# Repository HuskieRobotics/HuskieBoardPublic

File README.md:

# The Huskie Board
## Overview
The Huskie Board, designed by Team 3061, is an FRC qualified expansion board for the
NI roboRIO robotics controller. In addition to breaking out all available signals on the
MXP expansion port, this board uses a Parallax Propeller chip (8 symmetrical logical
cores with shared memory and peripheral access) to enable tasks such as advanced
data logging, on-field driver control and status, and NeoPixel control. Additional GPIO
and analog inputs are added with open source code to allow further customization.

## Firmware
The Huskie Board's firmware is stored on a 32 KB Flash chip. It can be upgraded over USB, and teams are welcome to load their own firmware. All Huskie Board firmware is stored in the `propeller firmware/` directory.

## roboRIO software
The LabView firmware is available in the `LabView/LabVIEW API/` directory. This includes examples in the `Examples/` folder, and the API source code in the `Huskie Board/` folder. See `install.txt` for more information.

Currently, the roboRIO API is only available for labview, though we hope to port it for C++ and Java soon.

## Hardware
The Huskie Board was designed in Eagle CAD, and sources are available in `Eagle CAD/projects/HuskieBoard/`.

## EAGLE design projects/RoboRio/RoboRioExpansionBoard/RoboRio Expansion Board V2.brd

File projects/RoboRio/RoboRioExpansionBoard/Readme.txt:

Fab Drawing                    | Fab.pdf
Assy Drawing                   | Assy.pdf
Fab Array Drawing, no holes    | Fab_1x3A.pdf
Fab Array Drawing, with holes  | Fab_1x3B.pdf

Top Copper                     | RoboRIO Expansion Board V2.GTL
Bottom Copper                  | RoboRIO Expansion Board V2.GBL
Top Silkscreen                 | RoboRIO Expansion Board V2.GTO
Top Paste                      | RoboRIO Expansion Board V2.GTP
Top Soldermask                 | RoboRIO Expansion Board V2.GTS
Bottom Soldermask              | RoboRIO Expansion Board V2.GBS
Drill File                     | RoboRIO Expansion Board V2.TXT
Mill Layer                     | RoboRIO Expansion Board V2.GML

centroid file                  | RoboRIO Expansion Board V2_centroid.csv

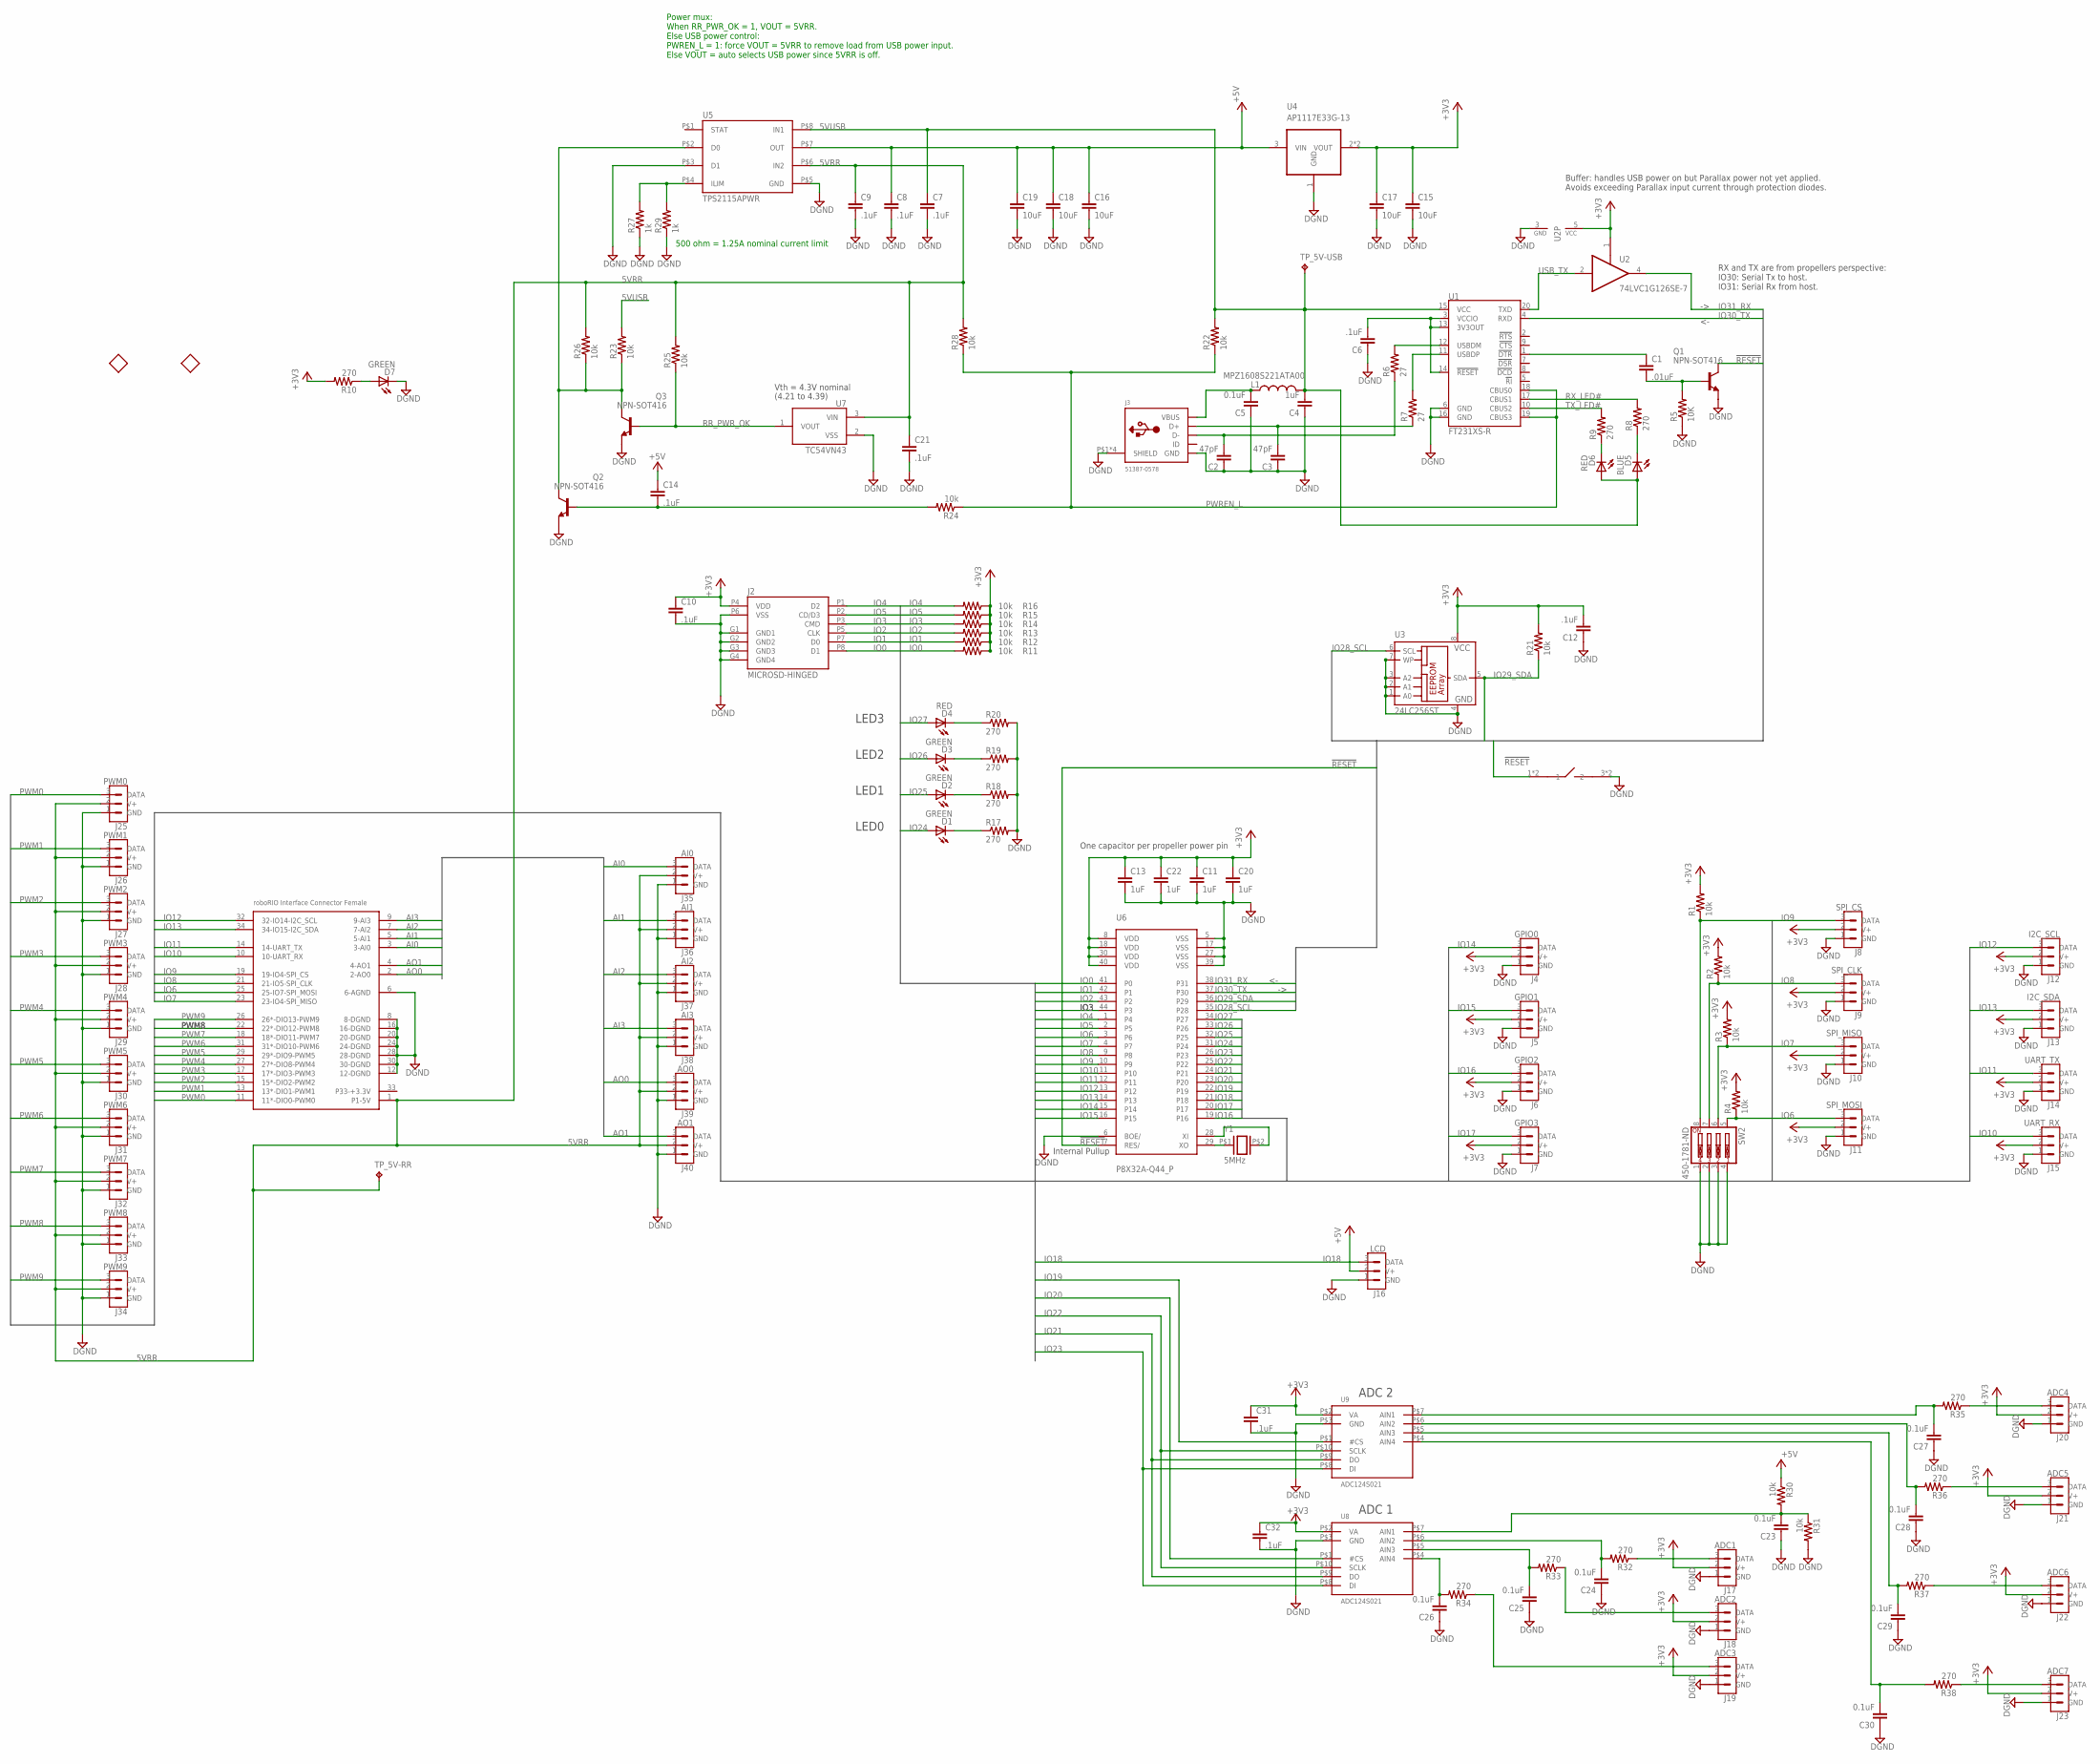
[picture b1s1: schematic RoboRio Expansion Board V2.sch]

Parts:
C1: .01uF; C0603K
C2, C3: 47pF; C0603K
C4, C11, C13, C20, C22: 1uF; C0603K
C5, C23, C24, C25, C26, C27, C28, C29, C30: 0.1uF; C0603K
C6, C7, C8, C9, C10, C12, C14, C21, C31, C32: .1uF; C0603K
C15, C16, C17, C18, C19: 10uF; C0805K
D1, D2, D3, D7: GREEN; CHIPLED_0603
D4, D6: RED; CHIPLED_0603
D5: BLUE; CHIPLED_0603
J1: RRINTERFACE-FEMALE; RRINT-FEMALE
J2: MICROSD-HINGED; MICRO_SD_HINGED_TYPE
J3: 51387-0578; USB-MINIB-0513870578
J4: GPIO0; 3PINPACKAGE
J5: GPIO1; 3PINPACKAGE
J6: GPIO2; 3PINPACKAGE
J7: GPIO3; 3PINPACKAGE
J8: SPI_CS; 3PINPACKAGE
J9: SPI_CLK; 3PINPACKAGE
J10: SPI_MISO; 3PINPACKAGE
J11: SPI_MOSI; 3PINPACKAGE
J12: I2C_SCL; 3PINPACKAGE
J13: I2C_SDA; 3PINPACKAGE
J14: UART_TX; 3PINPACKAGE
J15: UART_RX; 3PINPACKAGE
J16: LCD; 3PINPACKAGE
J17: ADC1; 3PINPACKAGE
J18: ADC2; 3PINPACKAGE
J19: ADC3; 3PINPACKAGE
J20: ADC4; 3PINPACKAGE
J21: ADC5; 3PINPACKAGE
J22: ADC6; 3PINPACKAGE
J23: ADC7; 3PINPACKAGE
J25: PWM0; 3PINPACKAGE
J26: PWM1; 3PINPACKAGE
J27: PWM2; 3PINPACKAGE
J28: PWM3; 3PINPACKAGE
J29: PWM4; 3PINPACKAGE
J30: PWM5; 3PINPACKAGE
J31: PWM6; 3PINPACKAGE
J32: PWM7; 3PINPACKAGE
J33: PWM8; 3PINPACKAGE
J34: PWM9; 3PINPACKAGE
J35: AI0; 3PINPACKAGE
J36: AI1; 3PINPACKAGE
J37: AI2; 3PINPACKAGE
J38: AI3; 3PINPACKAGE
J39: AO0; 3PINPACKAGE
J40: AO1; 3PINPACKAGE
L1: MPZ1608S221ATA00; 0603
Q1, Q2, Q3: NPN-SOT416; SC75_INFINEON
R1, R2, R3, R4, R11, R12, R13, R14, R15, R16, R21, R22, R23, R24, R25, R26, R28, R30, R31: 10k; R0603
R5: 10K; R0603
R6, R7: 27; R0603
R8, R9, R10, R17, R18, R19, R20, R32, R33, R34, R35, R36, R37, R38: 270; R0603
R27, R29: 1k; R0603
SW1: RESETBUTTON9001DEFAULT; RESETBUTTON9001
SW2: 450-1781-ND; EDG-04
TP_5V-RR, TP_5V-USB: TPPAD1-17; P1-17
U1: FT231XS-R; SSOP20_L
U2: 74LVC1G126SE-7; SC70-5
U3: 24LC256ST; TSSOP8
U4: AP1117E33G-13; SOT223; MPN AP1117E33G-13
U5: TPS2115APWR; TSSOP-8
U6: P8X32A-Q44_P; P8X32A-Q44
U7: TC54VN43; SOT23
U8, U9: ADC124S021; ADC124S021VSSOP
U$1, U$2: FIDUCIAL_DIAMOND; FIDUCIAL_40MIL_DIAMOND
Y1: 5MHz; HC\49US

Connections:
5VRR: C9.1, C21.1, J1.1 (P1-5V), J25.2 (V+), J26.2 (V+), J27.2 (V+), J28.2 (V+), J29.2 (V+), J30.2 (V+), J31.2 (V+), J32.2 (V+), J33.2 (V+), J34.2 (V+), J35.2 (V+), J36.2 (V+), J37.2 (V+), J38.2 (V+), J39.2 (V+), J40.2 (V+), R25.2, R26.2, R28.2, TP_5V-RR.TP, U5.P$6 (IN2), U7.3 (VIN)
5VUSB: C4.2, C7.1, D5.A, D6.A, L1.2, R22.2, R23.2, TP_5V-USB.TP, U1.15 (VCC), U5.P$8 (IN1)
!RESET: Q1.3 (C), SW1.1, SW1.2 (1), U6.7 (RES/)
+3V3: C10.1, C11.1, C12.2, C13.1, C15.1, C17.1, C20.1, C22.1, C31.1, C32.1, J2.P4 (VDD), J4.2 (V+), J5.2 (V+), J6.2 (V+), J7.2 (V+), J8.2 (V+), J9.2 (V+), J10.2 (V+), J11.2 (V+), J12.2 (V+), J13.2 (V+), J14.2 (V+), J15.2 (V+), J17.2 (V+), J18.2 (V+), J19.2 (V+), J20.2 (V+), J21.2 (V+), J22.2 (V+), J23.2 (V+), R1.2, R2.2, R3.2, R4.2, R10.2, R11.1, R12.1, R13.1, R14.1, R15.1, R16.1, R21.2, U2.1 (OE), U2.5 (VCC), U3.8 (VCC), U4.2 (VOUT), U4.4 (VOUT), U6.8 (VDD), U6.18 (VDD), U6.30 (VDD), U6.40 (VDD), U8.P$2 (VA), U9.P$2 (VA)
+5V: C8.1, C14.1, C16.1, C18.1, C19.1, J16.2 (V+), R30.1, U4.3 (VIN), U5.P$7 (OUT)
AI0: J1.3 (3-AI0), J35.3 (DATA)
AI1: J1.5 (5-AI1), J36.3 (DATA)
AI2: J1.7 (7-AI2), J37.3 (DATA)
AI3: J1.9 (9-AI3), J38.3 (DATA)
AO0: J1.2 (2-AO0), J39.3 (DATA)
AO1: J1.4 (4-AO1), J40.3 (DATA)
DGND: C2.1, C3.1, C4.1, C5.1, C6.1, C7.2, C8.2, C9.2, C10.2, C11.2, C12.1, C13.2, C15.2, C16.2, C17.2, C18.2, C19.2, C20.2, C21.2, C22.2, C23.1, C24.1, C25.1, C26.1, C27.1, C28.1, C29.1, C30.1, C31.2, C32.2, D7.C, J1.6 (6-AGND), J1.8 (8-DGND), J1.12 (12-DGND), J1.16 (16-DGND), J1.20 (20-DGND), J1.24 (24-DGND), J1.28 (28-DGND), J1.30 (30-DGND), J2.G1 (GND1), J2.G2 (GND2), J2.G3 (GND3), J2.G4 (GND4), J2.P6 (VSS), J3.GND, J3.P$1 (SHIELD), J3.P$2 (SHIELD), J3.P$3 (SHIELD), J3.P$4 (SHIELD), J4.1 (GND), J5.1 (GND), J6.1 (GND), J7.1 (GND), J8.1 (GND), J9.1 (GND), J10.1 (GND), J11.1 (GND), J12.1 (GND), J13.1 (GND), J14.1 (GND), J15.1 (GND), J16.1 (GND), J17.1 (GND), J18.1 (GND), J19.1 (GND), J20.1 (GND), J21.1 (GND), J22.1 (GND), J23.1 (GND), J25.1 (GND), J26.1 (GND), J27.1 (GND), J28.1 (GND), J29.1 (GND), J30.1 (GND), J31.1 (GND), J32.1 (GND), J33.1 (GND), J34.1 (GND), J35.1 (GND), J36.1 (GND), J37.1 (GND), J38.1 (GND), J39.1 (GND), J40.1 (GND), Q1.2 (E), Q2.2 (E), Q3.2 (E), R5.1, R17.2, R18.2, R19.2, R20.2, R27.1, R29.1, R31.2, SW1.3 (2), SW1.4 (2), SW2.1, SW2.2, SW2.3, SW2.4, U1.6 (GND), U1.16 (GND), U2.3 (GND), U3.1 (A0), U3.2 (A1), U3.3 (A2), U3.4 (GND), U3.7 (WP), U4.1 (GND), U5.P$3 (D1), U5.P$5 (GND), U6.5 (VSS), U6.6 (BOE/), U6.17 (VSS), U6.27 (VSS), U6.39 (VSS), U7.2 (VSS), U8.P$3 (GND), U9.P$3 (GND)
IO0: J2.P8 (D1), R11.2, U6.41 (P0)
IO1: J2.P7 (D0), R12.2, U6.42 (P1)
IO2: J2.P5 (CLK), R13.2, U6.43 (P2)
IO3: J2.P3 (CMD), R14.2, U6.44 (P3)
IO4: J2.P1 (D2), R16.2, U6.1 (P4)
IO5: J2.P2 (CD/D3), R15.2, U6.2 (P5)
IO6: J1.25 (25-IO7-SPI_MOSI), J11.3 (DATA), R4.1, SW2.5, U6.3 (P6)
IO7: J1.23 (23-IO4-SPI_MISO), J10.3 (DATA), R3.1, SW2.6, U6.4 (P7)
IO8: J1.21 (21-IO5-SPI_CLK), J9.3 (DATA), R2.1, SW2.7, U6.9 (P8)
IO9: J1.19 (19-IO4-SPI_CS), J8.3 (DATA), R1.1, SW2.8, U6.10 (P9)
IO10: J1.10 (10-UART_RX), J15.3 (DATA), U6.11 (P10)
IO11: J1.14 (14-UART_TX), J14.3 (DATA), U6.12 (P11)
IO12: J1.32 (32-IO14-I2C_SCL), J12.3 (DATA), U6.13 (P12)
IO13: J1.34 (34-IO15-I2C_SDA), J13.3 (DATA), U6.14 (P13)
IO14: J4.3 (DATA), U6.15 (P14)
IO15: J5.3 (DATA), U6.16 (P15)
IO16: J6.3 (DATA), U6.19 (P16)
IO17: J7.3 (DATA), U6.20 (P17)
IO18: J16.3 (DATA), U6.21 (P18)
IO19: U6.22 (P19), U9.P$1 (#CS)
IO20: U6.23 (P20), U8.P$1 (#CS)
IO21: U6.24 (P21), U8.P$9 (DO), U9.P$9 (DO)
IO22: U6.25 (P22), U8.P$10 (SCLK), U9.P$10 (SCLK)
IO23: U6.26 (P23), U8.P$8 (DI), U9.P$8 (DI)
IO24: D1.A, U6.31 (P24)
IO25: D2.A, U6.32 (P25)
IO26: D3.A, U6.33 (P26)
IO27: D4.A, U6.34 (P27)
IO28_SCL: U3.6 (SCL), U6.35 (P28)
IO29_SDA: R21.1, U3.5 (SDA), U6.36 (P29)
IO30_TX: U1.4 (RXD), U6.37 (P30)
IO31_RX: U2.4 (O), U6.38 (P31)
unnamed: C3.2, J3.D+, R7.1
unnamed: C2.2, J3.D-, R6.1
unnamed: C6.2, U1.3 (VCCIO), U1.13 (3V3OUT), U1.14 (!RESET)
unnamed: D7.A, R10.1
unnamed: C14.2, Q2.1 (B), R24.2
unnamed: J19.3 (DATA), R34.1
unnamed: J18.3 (DATA), R33.1
unnamed: C30.2, R38.2, U9.P$4 (AIN4)
unnamed: R27.2, R29.2, U5.P$4 (ILIM)
unnamed: D4.C, R20.1
unnamed: D1.C, R17.1
unnamed: D2.C, R18.1
unnamed: C26.2, R34.2, U8.P$4 (AIN4)
unnamed: C24.2, R32.2, U8.P$6 (AIN2)
unnamed: D3.C, R19.1
unnamed: D6.C, R9.1
unnamed: C1.1, U1.1 (!DTR)
unnamed: Q2.3 (C), Q3.3 (C), R23.1, R26.1, U5.P$2 (D0)
unnamed: C25.2, R33.2, U8.P$5 (AIN3)
unnamed: J17.3 (DATA), R32.1
unnamed: D5.C, R8.1
unnamed: R6.2, U1.12 (USBDM)
unnamed: C23.2, R30.2, R31.1, U8.P$7 (AIN1)
unnamed: C1.2, Q1.1 (B), R5.2
unnamed: R7.2, U1.11 (USBDP)
unnamed: C5.2, J3.VBUS, L1.1
unnamed: C29.2, R37.2, U9.P$5 (AIN3)
unnamed: U6.29 (XO), Y1.P$1 (1)
unnamed: J23.3 (DATA), R38.1
unnamed: J22.3 (DATA), R37.1
unnamed: U6.28 (XI), Y1.P$2 (2)
unnamed: C28.2, R36.2, U9.P$6 (AIN2)
unnamed: J21.3 (DATA), R36.1
unnamed: C27.2, R35.2, U9.P$7 (AIN1)
unnamed: J20.3 (DATA), R35.1
PWM0: J1.11 (11*-DIO0-PWM0), J25.3 (DATA)
PWM1: J1.13 (13*-DIO1-PWM1), J26.3 (DATA)
PWM2: J1.15 (15*-DIO2-PWM2), J27.3 (DATA)
PWM3: J1.17 (17*-DIO3-PWM3), J28.3 (DATA)
PWM4: J1.27 (27*-DIO8-PWM4), J29.3 (DATA)
PWM5: J1.29 (29*-DIO9-PWM5), J30.3 (DATA)
PWM6: J1.31 (31*-DIO10-PWM6), J31.3 (DATA)
PWM7: J1.18 (18*-DIO11-PWM7), J32.3 (DATA)
PWM8: J1.22 (22*-DIO12-PWM8), J33.3 (DATA)
PWM9: J1.26 (26*-DIO13-PWM9), J34.3 (DATA)
PWREN_L: R22.1, R24.1, R28.1, U1.18 (CBUS0), U1.19 (CBUS3)
RR_PWR_OK: Q3.1 (B), R25.1, U7.1 (VOUT)
RX_LED#: R8.2, U1.17 (CBUS1)
TX_LED#: R9.2, U1.10 (CBUS2)
USB_TX: U1.20 (TXD), U2.2 (I)

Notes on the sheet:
500 ohm = 1.25A nominal current limit
Power mux: When RR_PWR_OK = 1, VOUT = 5VRR. Else USB power control: PWREN_L = 1: force VOUT = 5VRR to remove load from USB power input. Else VOUT = auto selects USB power since 5VRR is off.
RX and TX are from propellers perspective: IO30: Serial Tx to host. IO31: Serial Rx from host.
Internal Pullup
Vth = 4.3V nominal
(4.21 to 4.39)
ADC 1
ADC 2
LED0
LED1
LED2
LED3
One capacitor per propeller power pin
Buffer: handles USB power on but Parallax power not yet applied. Avoids exceeding Parallax input current through protection diodes.

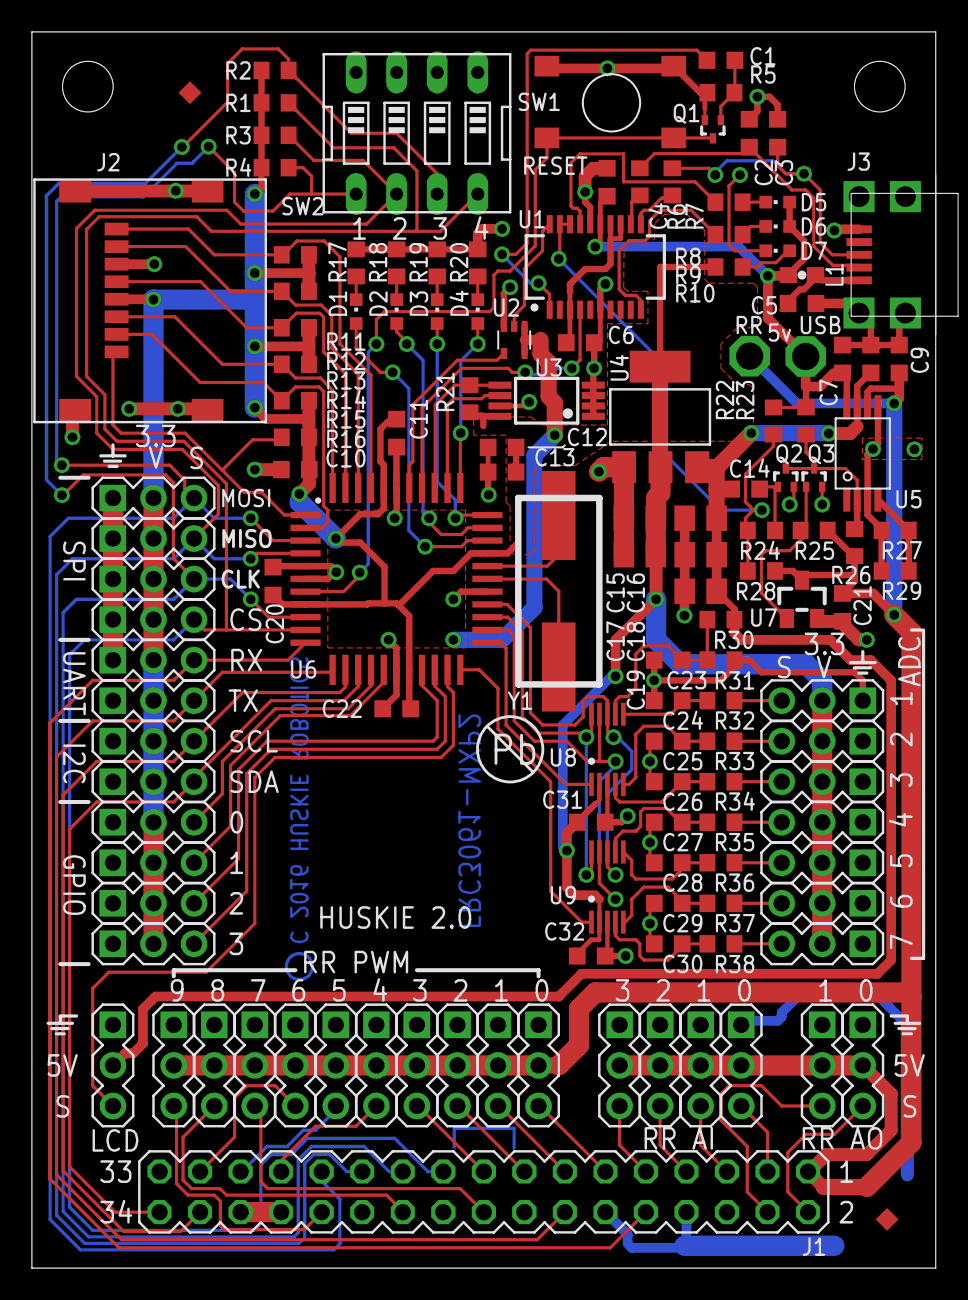
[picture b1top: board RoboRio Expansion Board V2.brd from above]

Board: 2 copper layers, 56.6 x 77.5 mm, 137 parts (0 on the bottom side), 94 nets.

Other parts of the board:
DRILEGEND: DRILEGEND

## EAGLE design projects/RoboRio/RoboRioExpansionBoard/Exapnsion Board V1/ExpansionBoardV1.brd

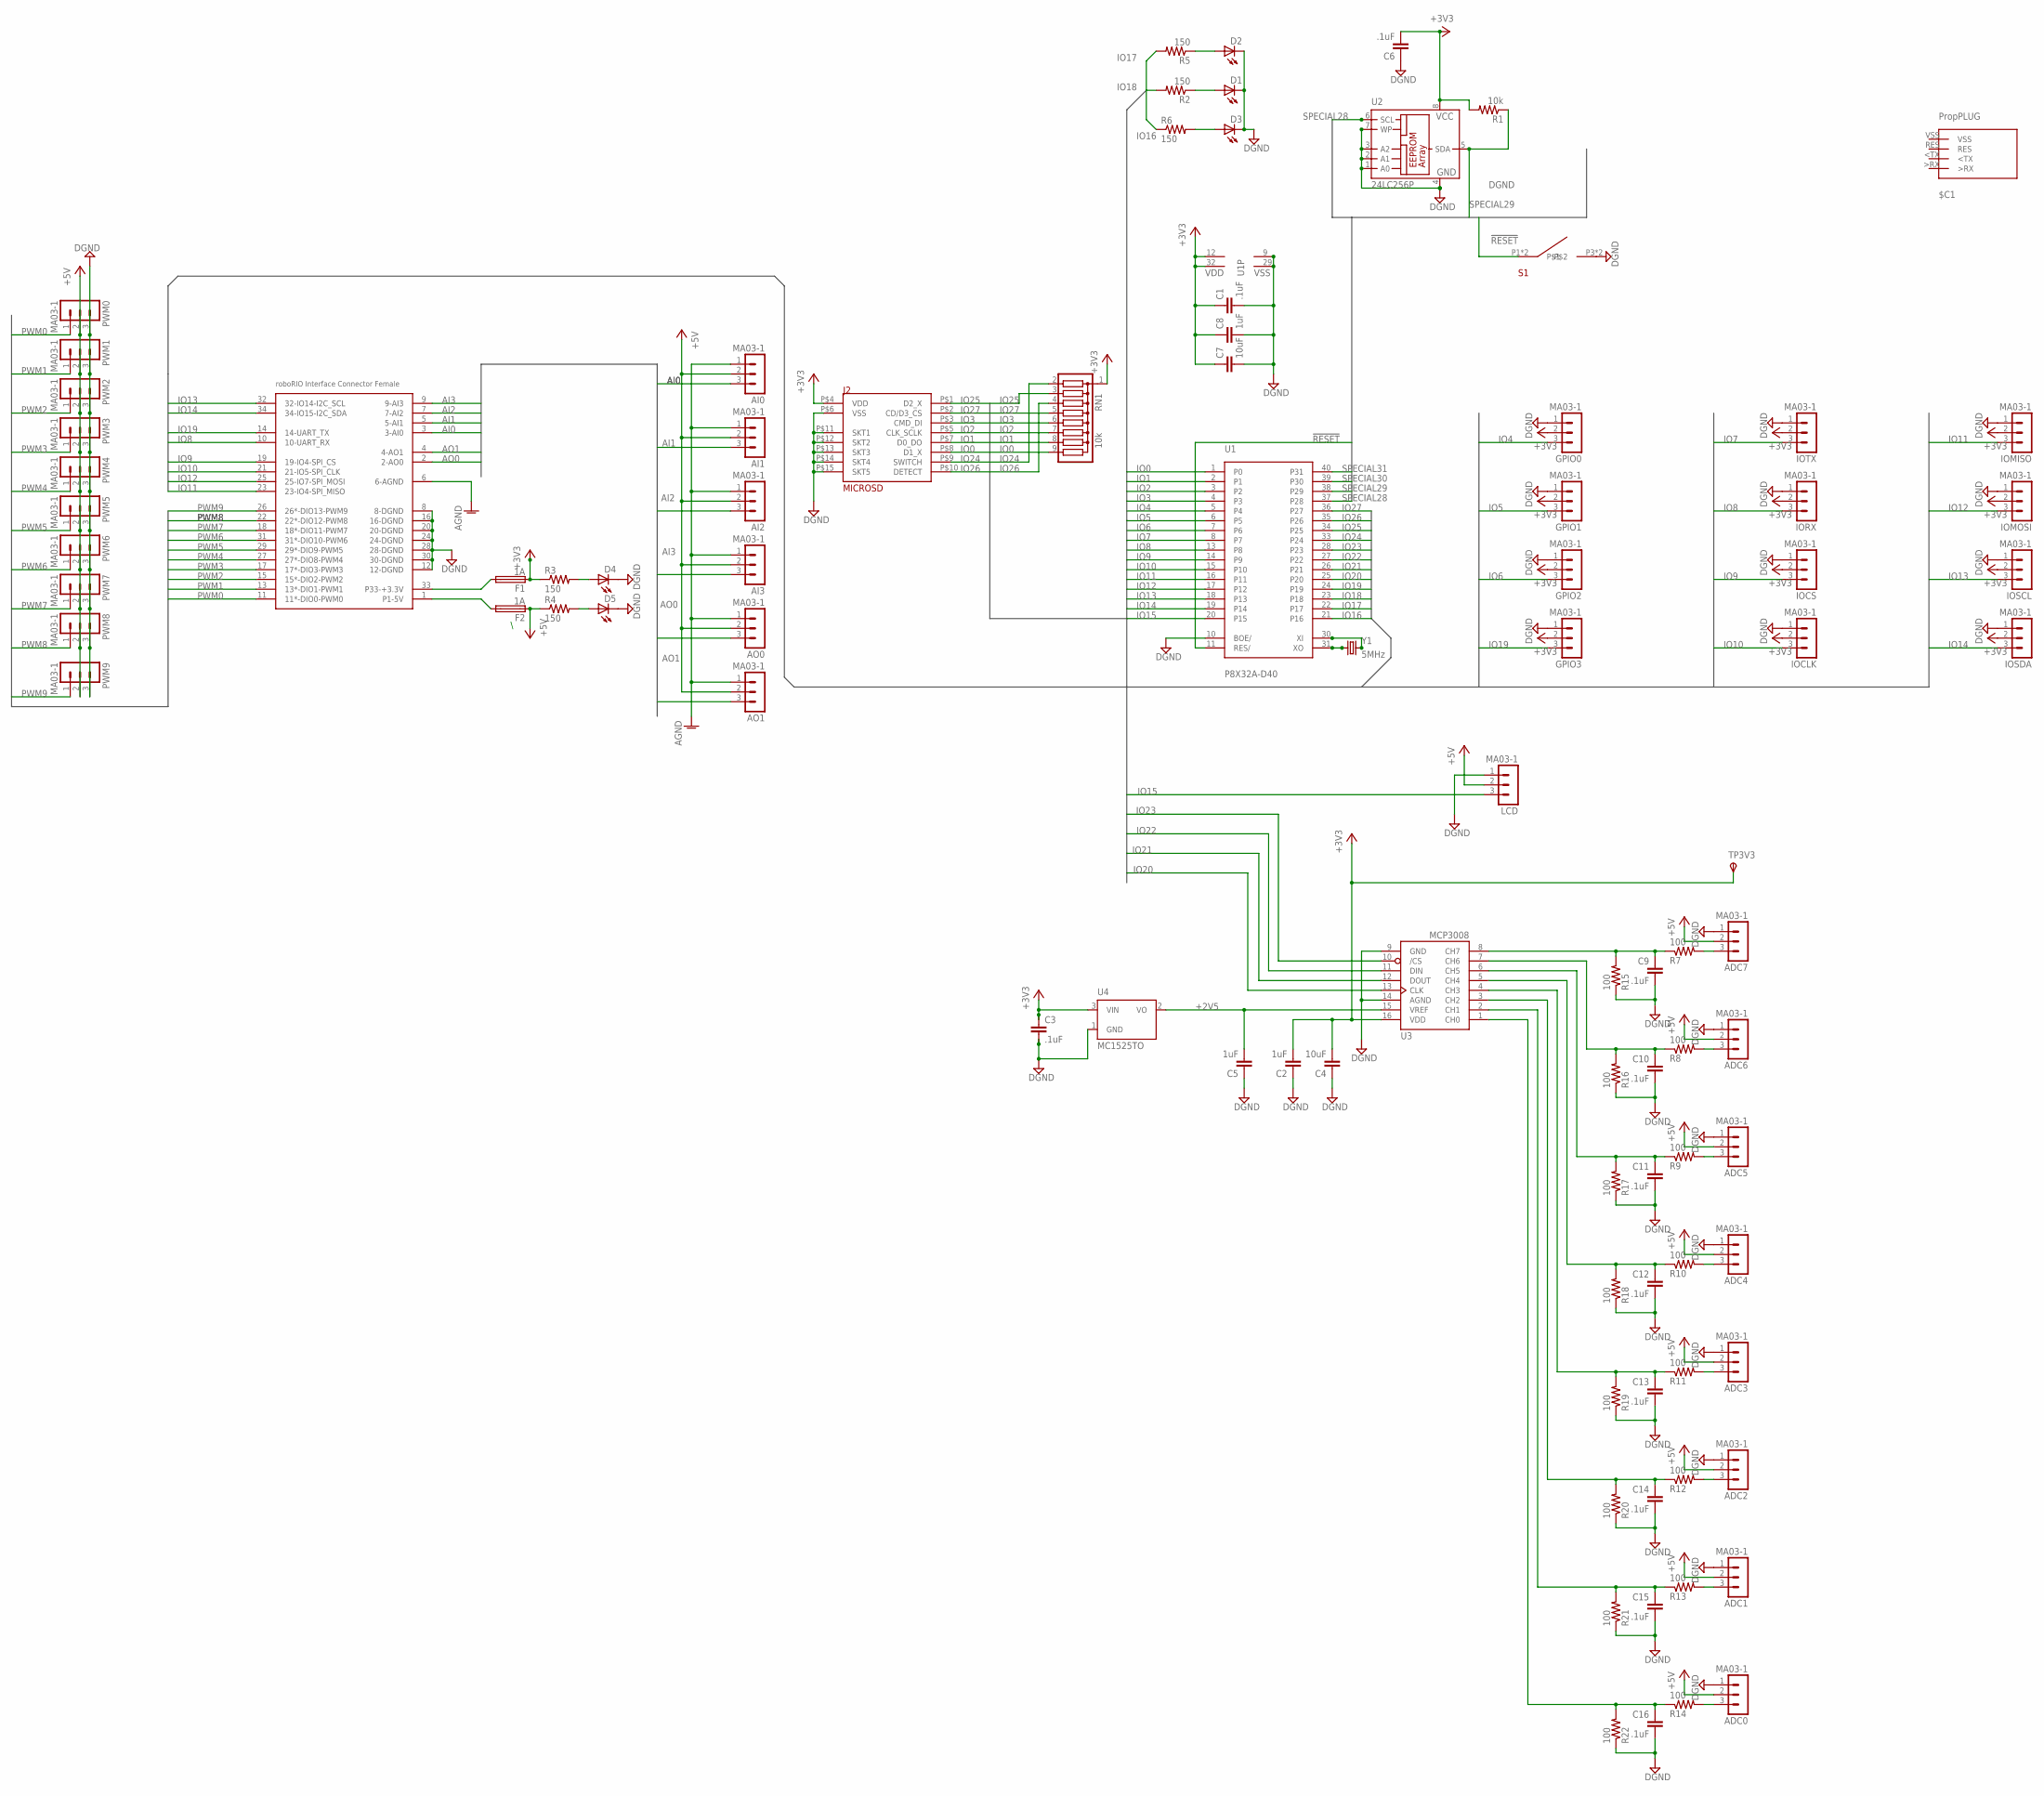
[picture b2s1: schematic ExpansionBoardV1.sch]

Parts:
ADC0, ADC1, ADC2, ADC3, ADC4, ADC5, ADC6, ADC7: MA03-1
AI0, AI1, AI2, AI3: MA03-1
AO0, AO1: MA03-1
C1, C3, C6, C9, C10, C11, C12, C13, C14, C15, C16: .1uF; C5B2.5
C2, C5, C8: 1uF; C5B2.5
C4, C7: 10uF; C5B2.5
D1, D2, D3, D4, D5: LED5MM
F1, F2: 1A; TR5
GPIO0, GPIO1, GPIO2, GPIO3: MA03-1
IOCLK: MA03-1
IOCS: MA03-1
IOMISO: MA03-1
IOMOSI: MA03-1
IORX: MA03-1
IOSCL: MA03-1
IOSDA: MA03-1
IOTX: MA03-1
J1: RRINTERFACE-FEMALE; RRINT-FEMALE
J2: MICROSD; MICRO_SD_PUSH-PUSH
LCD: MA03-1
P1: PROP_PLUG
PWM0, PWM1, PWM2, PWM3, PWM4, PWM5, PWM6, PWM7, PWM8, PWM9: MA03-1
R1: 10k; 0204/7
R2, R3, R4, R5, R6: 150; 0204/7
R7, R8, R9, R10, R11, R12, R13, R14, R15, R16, R17, R18, R19, R20, R21, R22: 100; 0204/7
RN1: 10k; SIL9
S1: BUTTON; RESETBUTTON300000MILLION
TP3V3: TPSPAD1-13; P1-13
U1: P8X32A-D40
U2: 24LC256P; DIL8
U3: MCP3008; DIL16
U4: MC1525TO; TO92
Y1: 5MHz; HC49U70

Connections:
!RESET: S1.P1, S1.P2, U1.11 (RES/)
+2V5: C5.2, U3.15 (VREF), U4.2 (VO)
+3V3: C1.1, C2.2, C3.1, C4.2, C6.2, C7.1, C8.1, F1.1, GPIO0.2, GPIO1.2, GPIO2.2, GPIO3.2, IOCLK.2, IOCS.2, IOMISO.2, IOMOSI.2, IORX.2, IOSCL.2, IOSDA.2, IOTX.2, J2.P$4 (VDD), R1.2, R3.1, RN1.1, TP3V3.TP, U1.12 (VDD), U1.32 (VDD), U2.8 (VCC), U3.16 (VDD), U4.3 (VIN)
+5V: ADC0.2, ADC1.2, ADC2.2, ADC3.2, ADC4.2, ADC5.2, ADC6.2, ADC7.2, AI0.2, AI1.2, AI2.2, AI3.2, AO0.2, AO1.2, F2.1, LCD.2, PWM0.2, PWM1.2, PWM2.2, PWM3.2, PWM4.2, PWM5.2, PWM6.2, PWM7.2, PWM8.2, PWM9.2, R4.1
AGND: AI0.1, AI1.1, AI2.1, AI3.1, AO0.1, AO1.1, J1.6 (6-AGND)
AI0: AI0.3, J1.3 (3-AI0)
AI1: AI1.3, J1.5 (5-AI1)
AI2: AI2.3, J1.7 (7-AI2)
AI3: AI3.3, J1.9 (9-AI3)
AO0: AO0.3, J1.2 (2-AO0)
AO1: AO1.3, J1.4 (4-AO1)
DGND: ADC0.1, ADC1.1, ADC2.1, ADC3.1, ADC4.1, ADC5.1, ADC6.1, ADC7.1, C1.2, C2.1, C3.2, C4.1, C5.1, C6.1, C7.2, C8.2, C9.2, C10.2, C11.2, C12.2, C13.2, C14.2, C15.2, C16.2, D1.K (C), D2.K (C), D3.K (C), D4.K (C), D5.K (C), GPIO0.1, GPIO1.1, GPIO2.1, GPIO3.1, IOCLK.1, IOCS.1, IOMISO.1, IOMOSI.1, IORX.1, IOSCL.1, IOSDA.1, IOTX.1, J1.8 (8-DGND), J1.12 (12-DGND), J1.16 (16-DGND), J1.20 (20-DGND), J1.24 (24-DGND), J1.28 (28-DGND), J1.30 (30-DGND), J2.P$6 (VSS), J2.P$11 (SKT1), J2.P$12 (SKT2), J2.P$13 (SKT3), J2.P$14 (SKT4), J2.P$15 (SKT5), LCD.1, PWM0.3, PWM1.3, PWM2.3, PWM3.3, PWM4.3, PWM5.3, PWM6.3, PWM7.3, PWM8.3, PWM9.3, R15.1, R16.1, R17.1, R18.1, R19.1, R20.1, R21.1, R22.1, S1.P3, S1.P4, U1.9 (VSS), U1.10 (BOE/), U1.29 (VSS), U2.1 (A0), U2.2 (A1), U2.3 (A2), U2.4 (GND), U2.7 (WP), U3.9 (GND), U3.14 (AGND), U4.1 (GND)
IO0: J2.P$8 (D1_X), RN1.9, U1.1 (P0)
IO1: J2.P$7 (D0_DO), RN1.8, U1.2 (P1)
IO2: J2.P$5 (CLK_SCLK), RN1.7, U1.3 (P2)
IO3: J2.P$3 (CMD_DI), RN1.6, U1.4 (P3)
IO4: GPIO0.3, U1.5 (P4)
IO5: GPIO1.3, U1.6 (P5)
IO6: GPIO2.3, U1.7 (P6)
IO7: IOTX.3, U1.8 (P7)
IO8: IORX.3, J1.10 (10-UART_RX), U1.13 (P8)
IO9: IOCS.3, J1.19 (19-IO4-SPI_CS), U1.14 (P9)
IO10: IOCLK.3, J1.21 (21-IO5-SPI_CLK), U1.15 (P10)
IO11: IOMISO.3, J1.23 (23-IO4-SPI_MISO), U1.16 (P11)
IO12: IOMOSI.3, J1.25 (25-IO7-SPI_MOSI), U1.17 (P12)
IO13: IOSCL.3, J1.32 (32-IO14-I2C_SCL), U1.18 (P13)
IO14: IOSDA.3, J1.34 (34-IO15-I2C_SDA), U1.19 (P14)
IO15: LCD.3, U1.20 (P15)
IO16: R6.1, U1.21 (P16)
IO17: R5.2, U1.22 (P17)
IO18: R2.2, U1.23 (P18)
IO19: GPIO3.3, J1.14 (14-UART_TX), U1.24 (P19)
IO20: U1.25 (P20), U3.13 (CLK)
IO21: U1.26 (P21), U3.12 (DOUT)
IO22: U1.27 (P22), U3.11 (DIN)
IO23: U1.28 (P23), U3.10 (/CS)
IO24: J2.P$9 (SWITCH), RN1.2, U1.33 (P24)
IO25: J2.P$1 (D2_X), RN1.3, U1.34 (P25)
IO26: J2.P$10 (DETECT), RN1.4, U1.35 (P26)
IO27: J2.P$2 (CD/D3_CS), RN1.5, U1.36 (P27)
L1: D4.A, R3.2
unnamed: U1.31 (XO), Y1.1
unnamed: U1.30 (XI), Y1.2
unnamed: D5.A, R4.2
unnamed: F1.2, J1.33 (P33-+3.3V)
unnamed: ADC1.3, R13.2
unnamed: C16.1, R14.1, R22.2, U3.1 (CH0)
unnamed: C15.1, R13.1, R21.2, U3.2 (CH1)
unnamed: C13.1, R11.1, R19.2, U3.4 (CH3)
unnamed: D3.A, R6.2
unnamed: D1.A, R2.1
unnamed: D2.A, R5.1
unnamed: F2.2, J1.1 (P1-5V)
unnamed: C14.1, R12.1, R20.2, U3.3 (CH2)
unnamed: C12.1, R10.1, R18.2, U3.5 (CH4)
unnamed: ADC2.3, R12.2
unnamed: ADC3.3, R11.2
unnamed: ADC4.3, R10.2
unnamed: C11.1, R9.1, R17.2, U3.6 (CH5)
unnamed: ADC5.3, R9.2
unnamed: ADC0.3, R14.2
unnamed: C9.1, R7.1, R15.2, U3.8 (CH7)
unnamed: ADC6.3, R8.2
unnamed: ADC7.3, R7.2
unnamed: C10.1, R8.1, R16.2, U3.7 (CH6)
PWM0: J1.11 (11*-DIO0-PWM0), PWM0.1
PWM1: J1.13 (13*-DIO1-PWM1), PWM1.1
PWM2: J1.15 (15*-DIO2-PWM2), PWM2.1
PWM3: J1.17 (17*-DIO3-PWM3), PWM3.1
PWM4: J1.27 (27*-DIO8-PWM4), PWM4.1
PWM5: J1.29 (29*-DIO9-PWM5), PWM5.1
PWM6: J1.31 (31*-DIO10-PWM6), PWM6.1
PWM7: J1.18 (18*-DIO11-PWM7), PWM7.1
PWM8: J1.22 (22*-DIO12-PWM8), PWM8.1
PWM9: J1.26 (26*-DIO13-PWM9), PWM9.1
SPECIAL28: U1.37 (P28), U2.6 (SCL)
SPECIAL29: R1.1, U1.38 (P29), U2.5 (SDA)
SPECIAL30: U1.39 (P30)
SPECIAL31: U1.40 (P31)

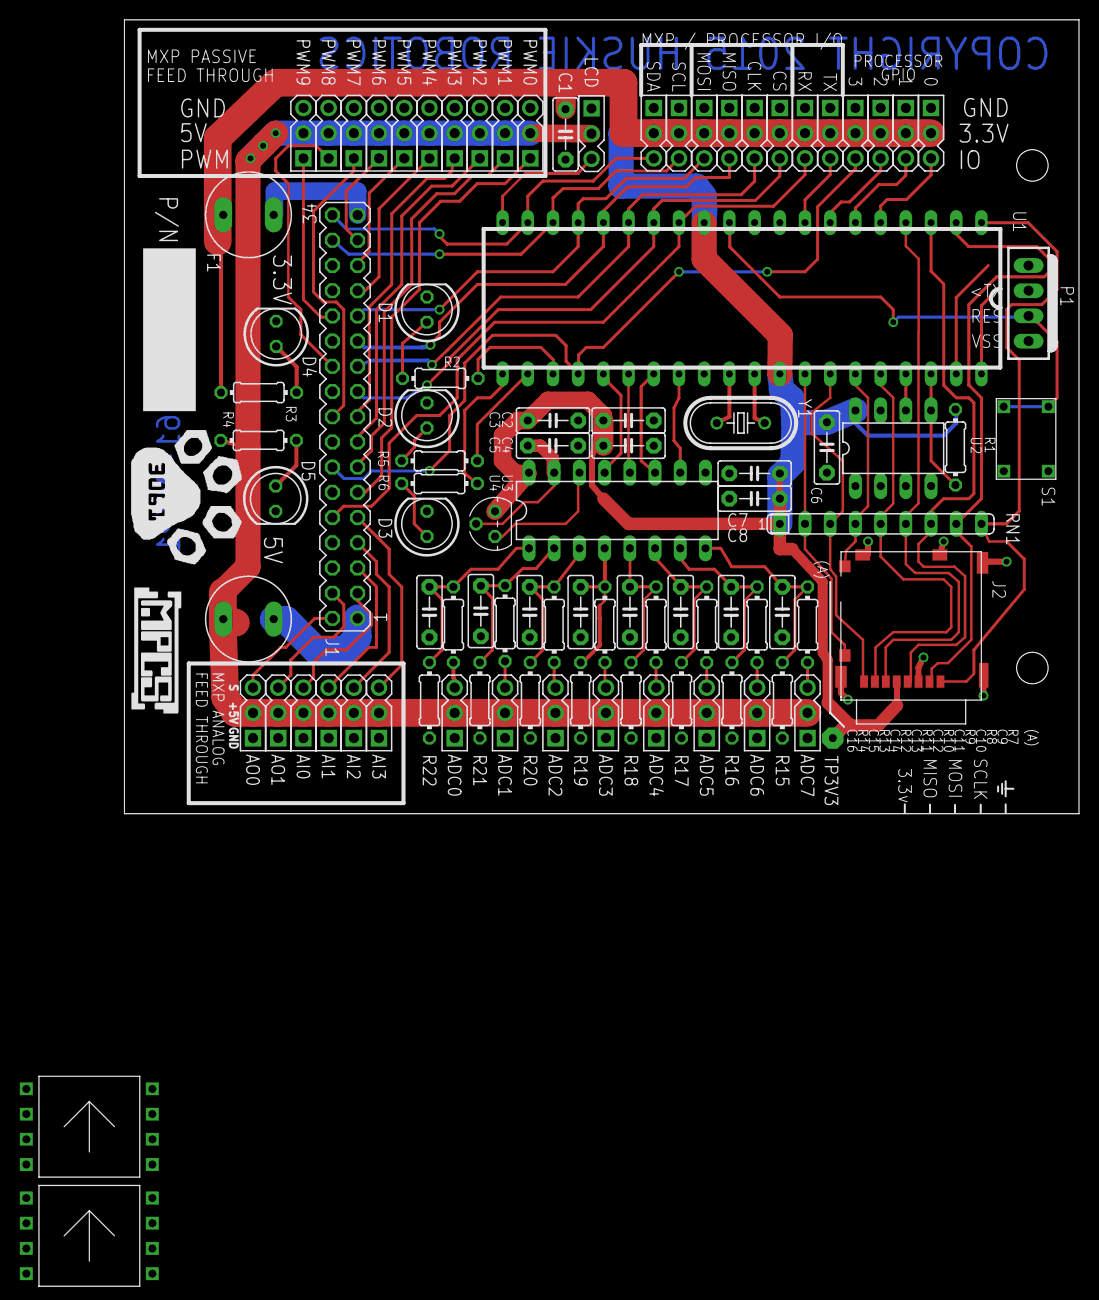
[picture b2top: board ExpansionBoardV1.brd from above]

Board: 2 copper layers, 96.2 x 80.0 mm, 96 parts (0 on the bottom side), 77 nets.

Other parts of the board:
DRILEGEND: DRILEGEND
U$1, U$2: 24LC256(MICROCHIP); 24LC256

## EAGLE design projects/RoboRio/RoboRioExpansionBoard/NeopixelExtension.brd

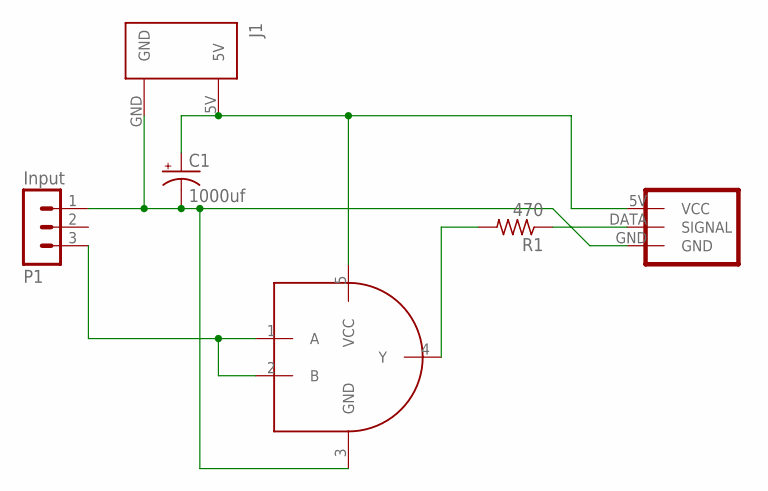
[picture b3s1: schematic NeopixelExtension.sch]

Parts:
C1: 1000uf; E5-10,5
J1: POWER
P1: Input; MA03-1
R1: 470; R1206
U1: 74AHCT1G08; SOT25
U$2: NEOPIXEL1; NEODIRECTSOLDERORMA03-1

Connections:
GND: C1.-, J1.GND, P1.1, U1.3 (GND), U$2.GND
unnamed: R1.1, U$2.DATA (SIGNAL)
unnamed: P1.3, U1.1 (A), U1.2 (B)
unnamed: R1.2, U1.4 (Y)
VCC: C1.+, J1.5V, U1.5 (VCC), U$2.5V (VCC)

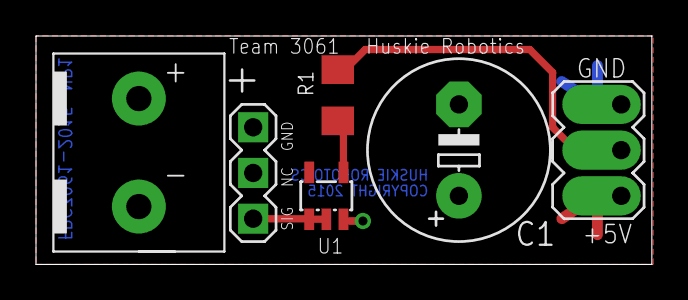
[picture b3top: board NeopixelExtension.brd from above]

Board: 2 copper layers, 34.2 x 12.7 mm, 6 parts (0 on the bottom side), 5 nets.

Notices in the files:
projects/RoboRio/RoboRioExpansionBoard/Exapnsion Board V1/ExpansionBoardV1.brd:
COPYRIGHT 2015 HUSKIE ROBOTICS
parts and their libraries:
m-pad-2.1: License : GNU General Public License version 2 (see bottom)
SparkFun-DigitalIC: Licensing: Creative Commons ShareAlike 4.0 International - https://creativecommons.org/licenses/by-sa/4.0
